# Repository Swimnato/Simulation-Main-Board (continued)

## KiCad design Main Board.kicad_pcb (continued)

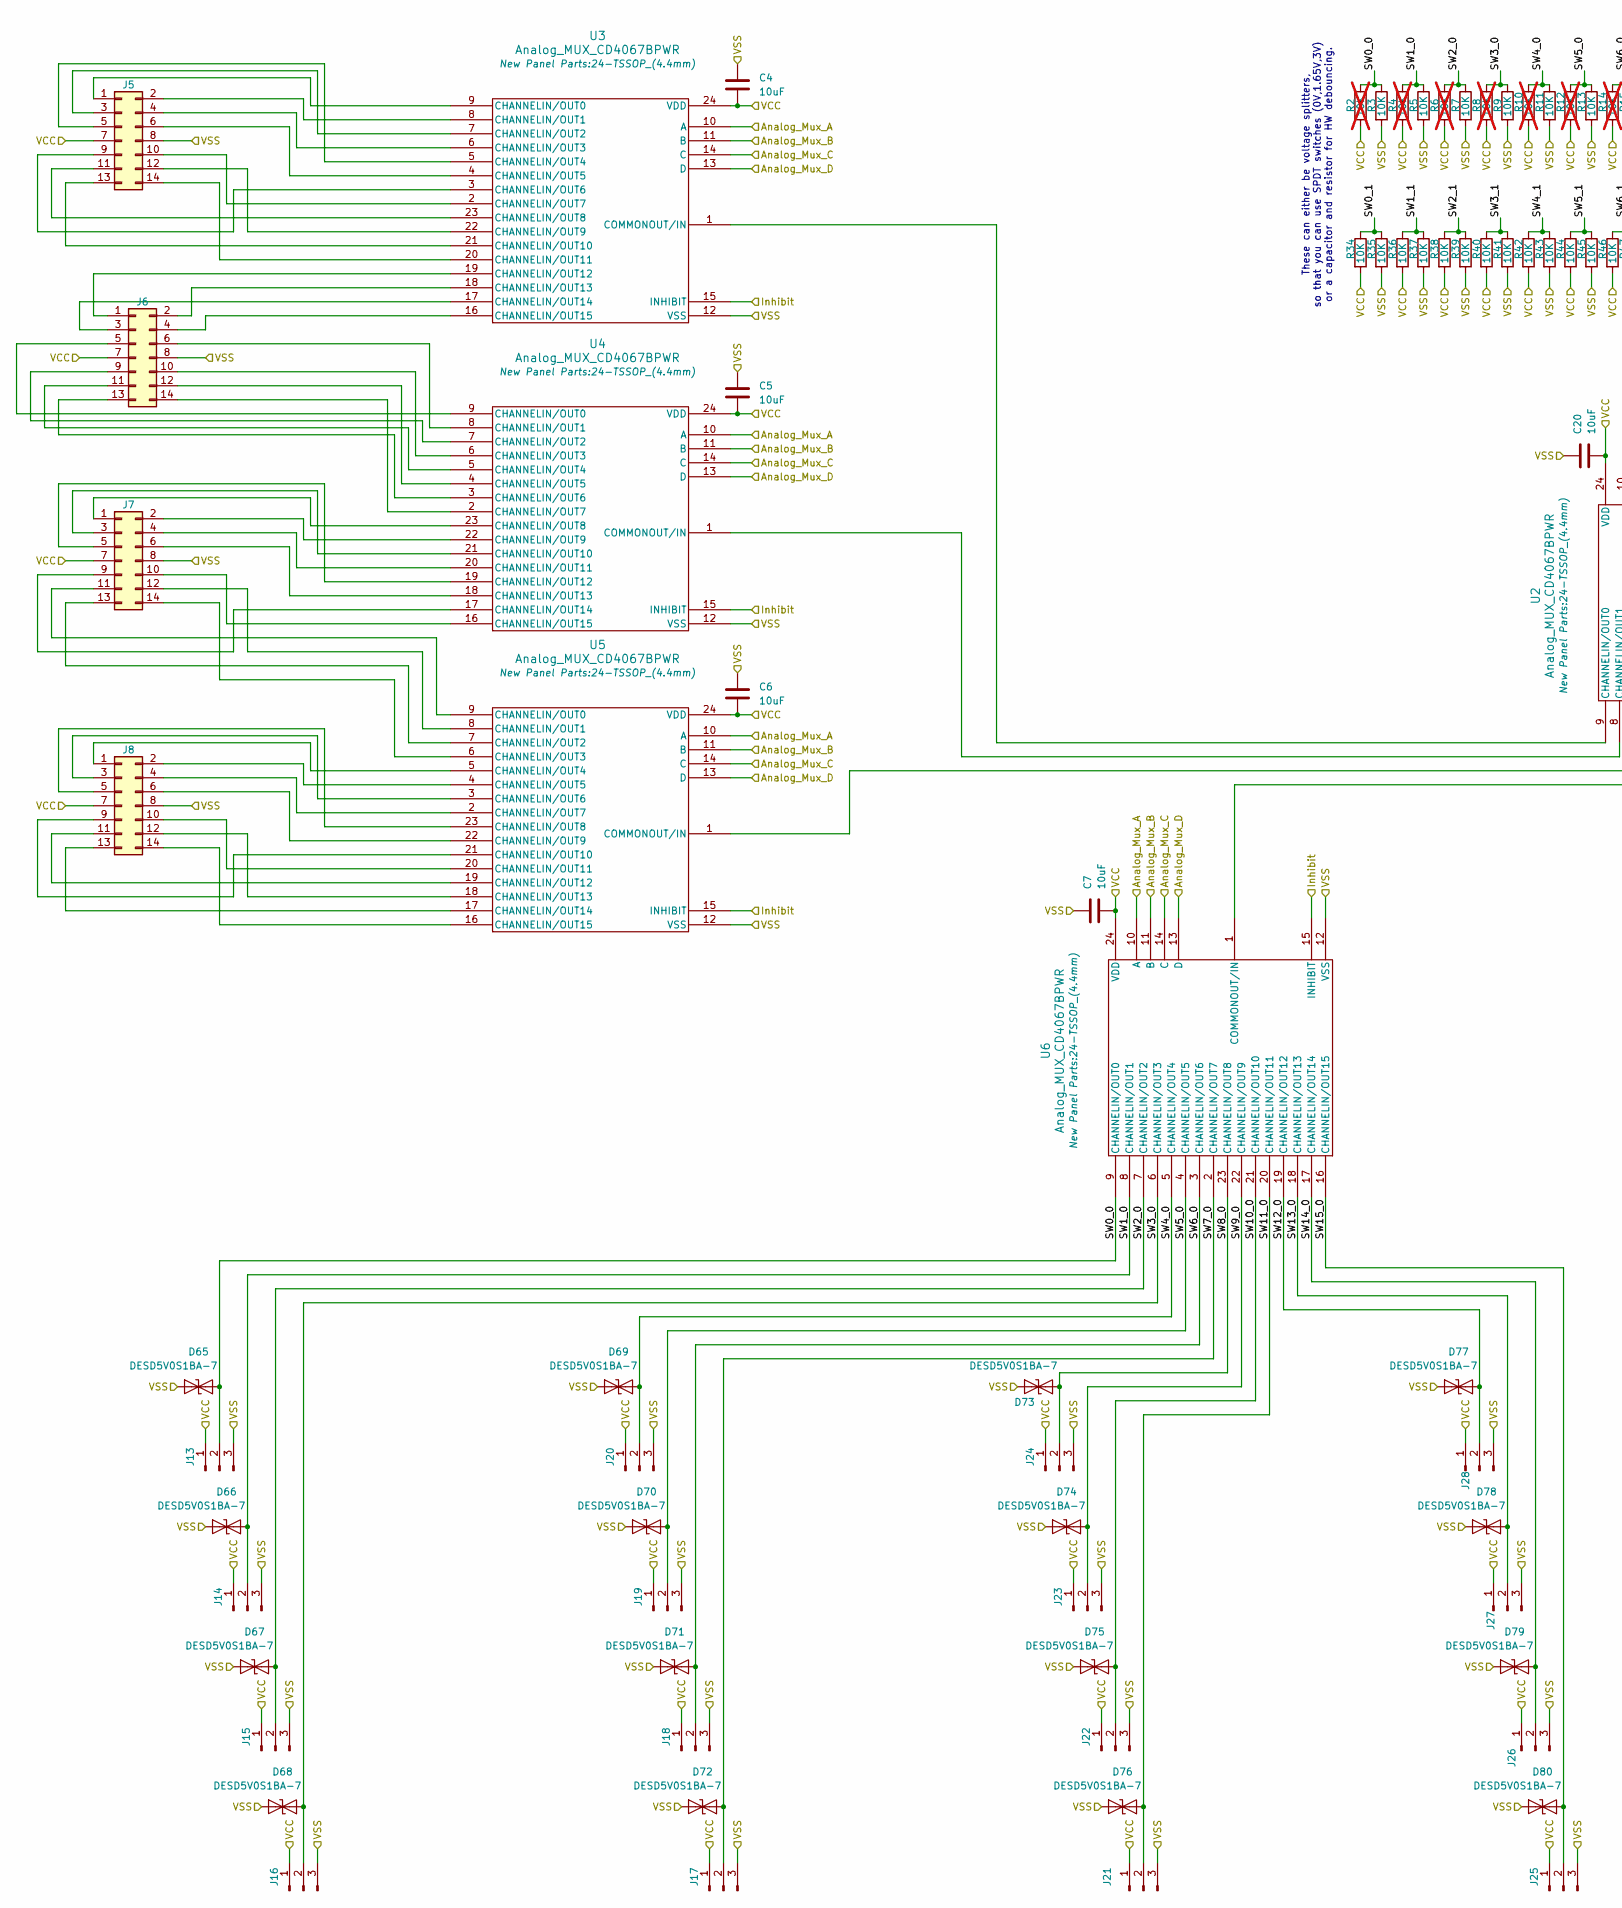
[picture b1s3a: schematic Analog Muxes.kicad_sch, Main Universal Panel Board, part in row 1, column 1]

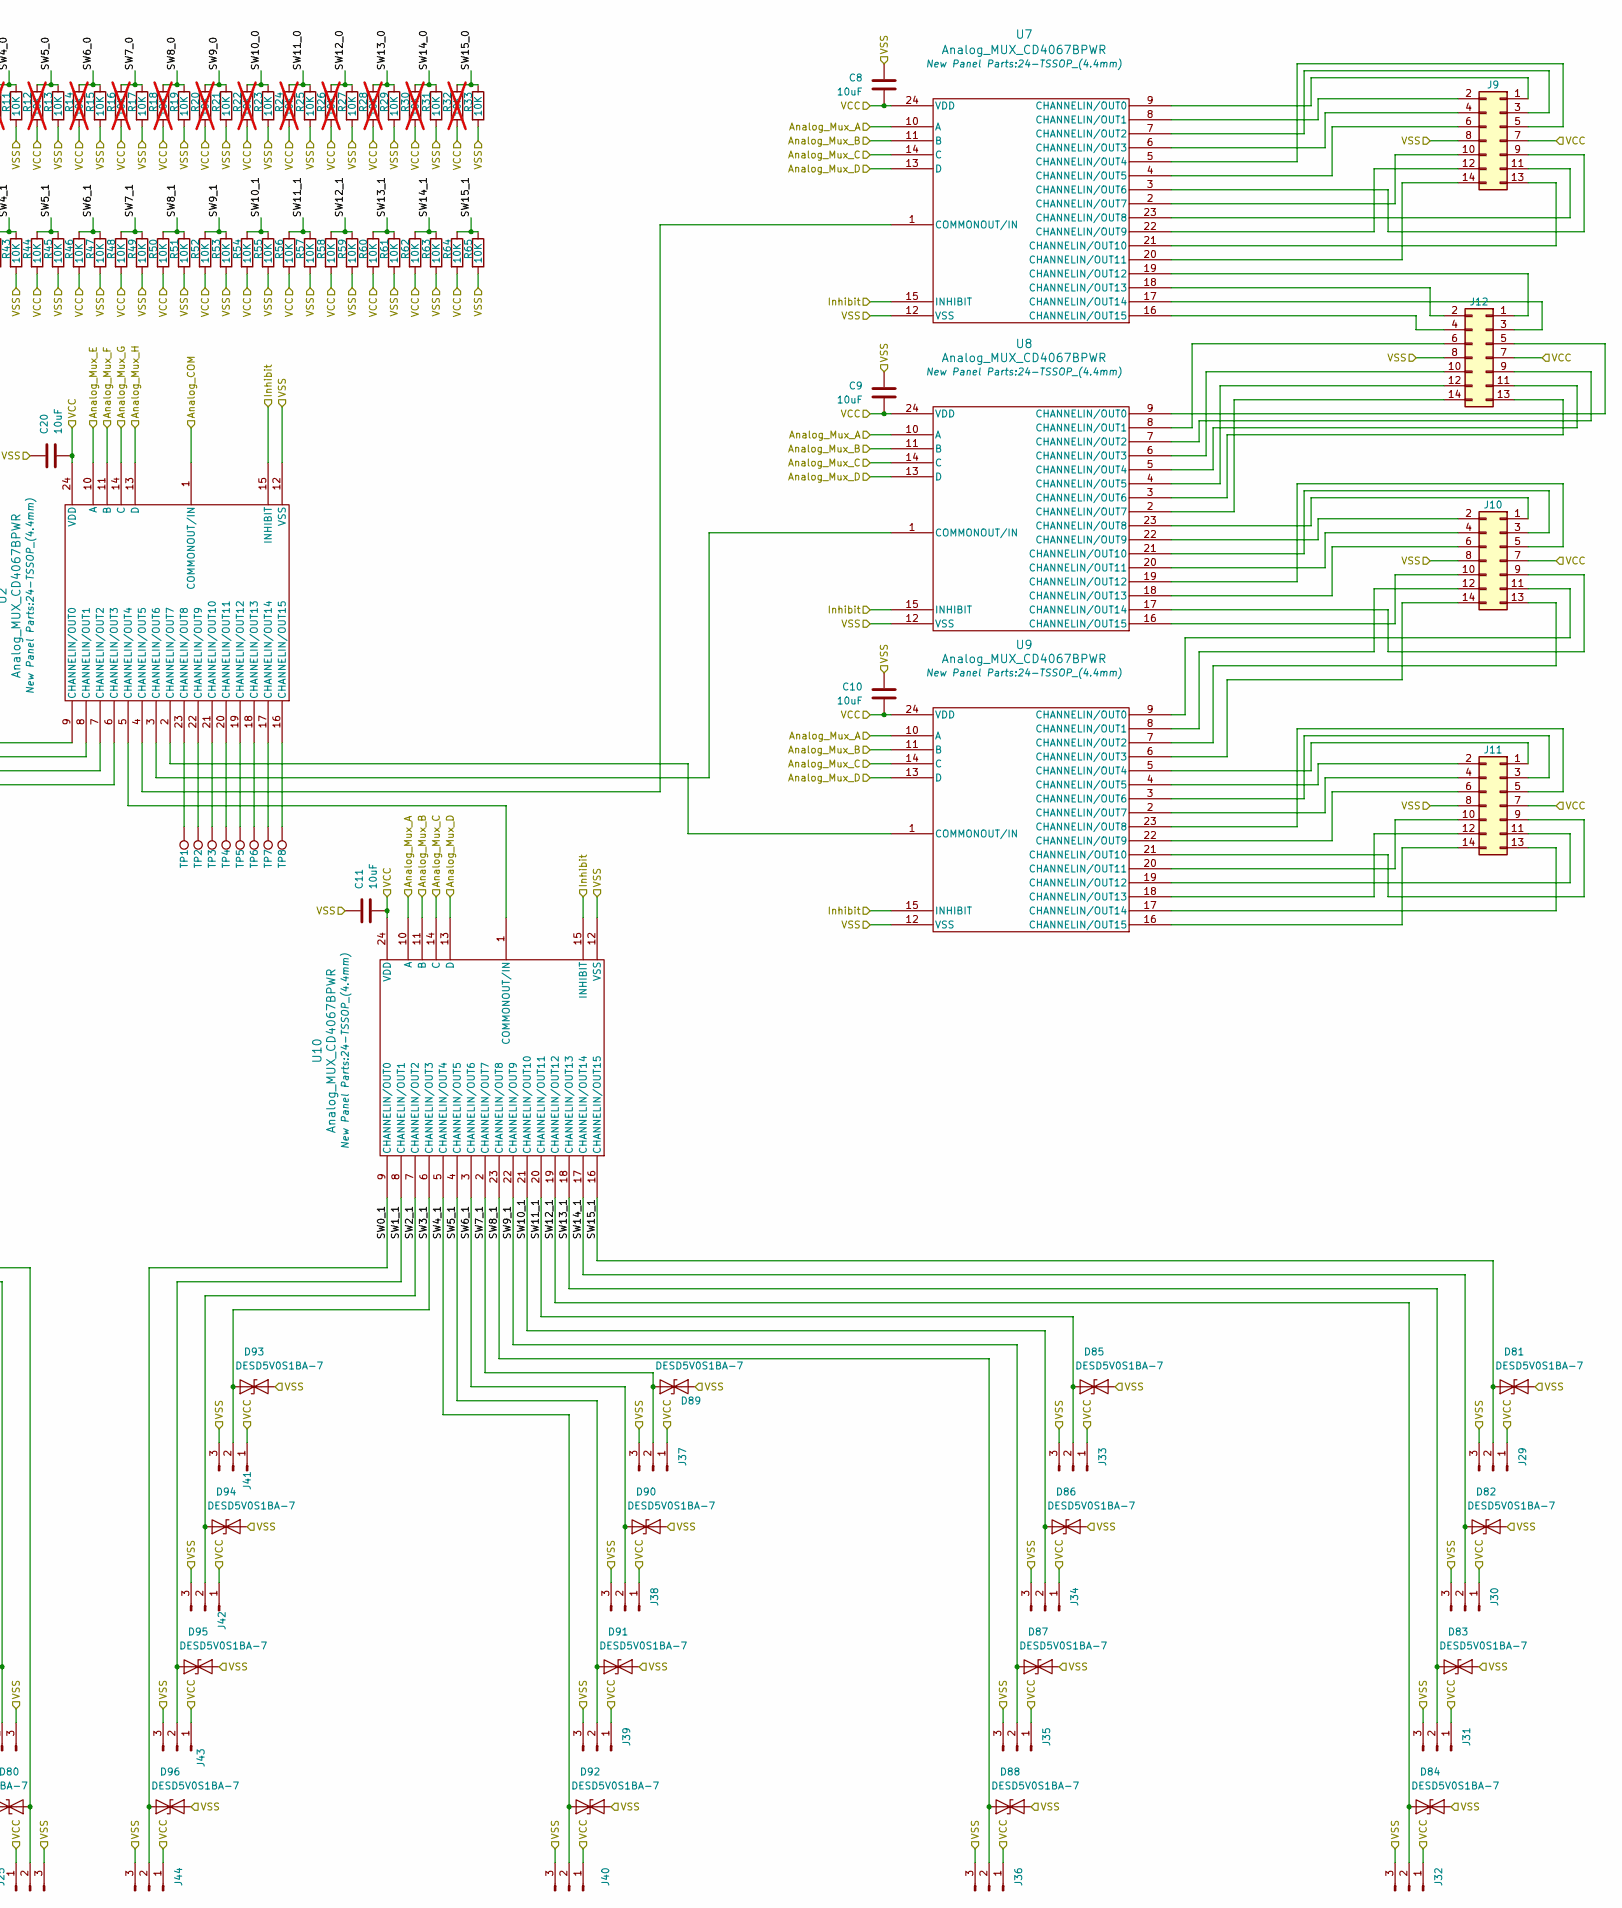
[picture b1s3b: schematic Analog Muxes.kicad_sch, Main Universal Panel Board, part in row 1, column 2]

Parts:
C4, C5, C6, C7, C8, C9, C10, C11, C20: 10uF; C_0805_2012Metric_Pad1.18x1.45mm_HandSolder
D65, D66, D67, D68, D69, D70, D71, D72, D73, D74, D75, D76, D77, D78, D79, D80, D81, D82, D83, D84, D85, D86, D87, D88, D89, D90, D91, D92, D93, D94, D95, D96: DESD5V0S1BA-7; D_SOD-323
J5, J6, J7, J8, J9, J10, J11, J12: Conn_02x07_Odd_Even; IDC-Header_2x07_P2.54mm_Vertical
J13, J14, J15, J16, J17, J18, J19, J20, J21, J22, J23, J24, J25, J26, J27, J28, J29, J30, J31, J32, J33, J34, J35, J36, J37, J38, J39, J40, J41, J42, J43, J44: Conn_01x03_Pin; JST_PH_B3B-PH-K_1x03_P2.00mm_Vertical
R2, R4, R6, R8, R10, R12, R14, R16, R18, R20, R22, R24, R26, R28, R30, R32: 10K; R_0603_1608Metric; not fitted
R3, R5, R7, R9, R11, R13, R15, R17, R19, R21, R23, R25, R27, R29, R31, R33, R34, R35, R36, R37, R38, R39, R40, R41, R42, R43, R44, R45, R46, R47, R48, R49, R50, R51, R52, R53, R54, R55, R56, R57, R58, R59, R60, R61, R62, R63, R64, R65: 10K; R_0603_1608Metric
TP1, TP2, TP3, TP4, TP5, TP6, TP7, TP8: TestPoint; Pin_D1.0mm_L10.0mm
U2, U3, U4, U5, U6, U7, U8, U9, U10: Analog_MUX_CD4067BPWR; 24-TSSOP_(4.4mm); Manufacturer Part Number CD4067BPWR

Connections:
+3.3V: C4.2, C5.2, C6.2, C7.2, C8.2, C9.2, C10.2, C11.2, C20.2, J5.7, J6.7, J7.7, J8.7, J9.7, J10.7, J11.7, J12.7, J13.1, J14.1, J15.1, J16.1, J17.1, J18.1, J19.1, J20.1, J21.1, J22.1, J23.1, J24.1, J25.1, J26.1, J27.1, J28.1, J29.1, J30.1, J31.1, J32.1, J33.1, J34.1, J35.1, J36.1, J37.1, J38.1, J39.1, J40.1, J41.1, J42.1, J43.1, J44.1, R2.2, R4.2, R6.2, R8.2, R10.2, R12.2, R14.2, R16.2, R18.2, R20.2, R22.2, R24.2, R26.2, R28.2, R30.2, R32.2, R34.2, R36.2, R38.2, R40.2, R42.2, R44.2, R46.2, R48.2, R50.2, R52.2, R54.2, R56.2, R58.2, R60.2, R62.2, R64.2, U2.24 (VDD), U3.24 (VDD), U4.24 (VDD), U5.24 (VDD), U6.24 (VDD), U7.24 (VDD), U8.24 (VDD), U9.24 (VDD), U10.24 (VDD); also elsewhere on the board
/Analog Input Mux/Analog_COM: U2.1 (COMMONOUT/IN); also elsewhere on the board
/Analog Input Mux/Analog_Mux_A: U3.10 (A), U4.10 (A), U5.10 (A), U6.10 (A), U7.10 (A), U8.10 (A), U9.10 (A), U10.10 (A); also elsewhere on the board
/Analog Input Mux/Analog_Mux_B: U3.11 (B), U4.11 (B), U5.11 (B), U6.11 (B), U7.11 (B), U8.11 (B), U9.11 (B), U10.11 (B); also elsewhere on the board
/Analog Input Mux/Analog_Mux_C: U3.14 (C), U4.14 (C), U5.14 (C), U6.14 (C), U7.14 (C), U8.14 (C), U9.14 (C), U10.14 (C); also elsewhere on the board
/Analog Input Mux/Analog_Mux_D: U3.13 (D), U4.13 (D), U5.13 (D), U6.13 (D), U7.13 (D), U8.13 (D), U9.13 (D), U10.13 (D); also elsewhere on the board
/Analog Input Mux/Analog_Mux_E: U2.10 (A); also elsewhere on the board
/Analog Input Mux/Analog_Mux_F: U2.11 (B); also elsewhere on the board
/Analog Input Mux/Analog_Mux_G: U2.14 (C); also elsewhere on the board
/Analog Input Mux/Analog_Mux_H: U2.13 (D); also elsewhere on the board
/Analog Input Mux/Inhibit: U2.15 (INHIBIT), U3.15 (INHIBIT), U4.15 (INHIBIT), U5.15 (INHIBIT), U6.15 (INHIBIT), U7.15 (INHIBIT), U8.15 (INHIBIT), U9.15 (INHIBIT), U10.15 (INHIBIT); also elsewhere on the board
/Analog Input Mux/SW0_0: D65.1 (A1), J13.2, R2.1, R3.1, U6.9 (CHANNELIN/OUT0)
/Analog Input Mux/SW0_1: D96.1 (A1), J44.2, R34.1, R35.1, U10.9 (CHANNELIN/OUT0)
/Analog Input Mux/SW1_0: D66.1 (A1), J14.2, R4.1, R5.1, U6.8 (CHANNELIN/OUT1)
/Analog Input Mux/SW1_1: D95.1 (A1), J43.2, R36.1, R37.1, U10.8 (CHANNELIN/OUT1)
/Analog Input Mux/SW2_0: D67.1 (A1), J15.2, R6.1, R7.1, U6.7 (CHANNELIN/OUT2)
/Analog Input Mux/SW2_1: D94.1 (A1), J42.2, R38.1, R39.1, U10.7 (CHANNELIN/OUT2)
/Analog Input Mux/SW3_0: D68.1 (A1), J16.2, R8.1, R9.1, U6.6 (CHANNELIN/OUT3)
/Analog Input Mux/SW3_1: D93.1 (A1), J41.2, R40.1, R41.1, U10.6 (CHANNELIN/OUT3)
/Analog Input Mux/SW4_0: D69.1 (A1), J20.2, R10.1, R11.1, U6.5 (CHANNELIN/OUT4)
/Analog Input Mux/SW4_1: D92.1 (A1), J40.2, R42.1, R43.1, U10.5 (CHANNELIN/OUT4)
/Analog Input Mux/SW5_0: D70.1 (A1), J19.2, R12.1, R13.1, U6.4 (CHANNELIN/OUT5)
/Analog Input Mux/SW5_1: D91.1 (A1), J39.2, R44.1, R45.1, U10.4 (CHANNELIN/OUT5)
/Analog Input Mux/SW6_0: D71.1 (A1), J18.2, R14.1, R15.1, U6.3 (CHANNELIN/OUT6)
/Analog Input Mux/SW6_1: D90.1 (A1), J38.2, R46.1, R47.1, U10.3 (CHANNELIN/OUT6)
/Analog Input Mux/SW7_0: D72.1 (A1), J17.2, R16.1, R17.1, U6.2 (CHANNELIN/OUT7)
/Analog Input Mux/SW7_1: D89.1 (A1), J37.2, R48.1, R49.1, U10.2 (CHANNELIN/OUT7)
/Analog Input Mux/SW8_0: D73.1 (A1), J24.2, R18.1, R19.1, U6.23 (CHANNELIN/OUT8)
/Analog Input Mux/SW8_1: D88.1 (A1), J36.2, R50.1, R51.1, U10.23 (CHANNELIN/OUT8)
/Analog Input Mux/SW9_0: D74.1 (A1), J23.2, R20.1, R21.1, U6.22 (CHANNELIN/OUT9)
/Analog Input Mux/SW9_1: D87.1 (A1), J35.2, R52.1, R53.1, U10.22 (CHANNELIN/OUT9)
/Analog Input Mux/SW10_0: D75.1 (A1), J22.2, R22.1, R23.1, U6.21 (CHANNELIN/OUT10)
/Analog Input Mux/SW10_1: D86.1 (A1), J34.2, R54.1, R55.1, U10.21 (CHANNELIN/OUT10)
/Analog Input Mux/SW11_0: D76.1 (A1), J21.2, R24.1, R25.1, U6.20 (CHANNELIN/OUT11)
/Analog Input Mux/SW11_1: D85.1 (A1), J33.2, R56.1, R57.1, U10.20 (CHANNELIN/OUT11)
/Analog Input Mux/SW12_0: D77.1 (A1), J28.2, R26.1, R27.1, U6.19 (CHANNELIN/OUT12)
/Analog Input Mux/SW12_1: D84.1 (A1), J32.2, R58.1, R59.1, U10.19 (CHANNELIN/OUT12)
/Analog Input Mux/SW13_0: D78.1 (A1), J27.2, R28.1, R29.1, U6.18 (CHANNELIN/OUT13)
/Analog Input Mux/SW13_1: D83.1 (A1), J31.2, R60.1, R61.1, U10.18 (CHANNELIN/OUT13)
/Analog Input Mux/SW14_0: D79.1 (A1), J26.2, R30.1, R31.1, U6.17 (CHANNELIN/OUT14)
/Analog Input Mux/SW14_1: D82.1 (A1), J30.2, R62.1, R63.1, U10.17 (CHANNELIN/OUT14)
/Analog Input Mux/SW15_0: D80.1 (A1), J25.2, R32.1, R33.1, U6.16 (CHANNELIN/OUT15)
/Analog Input Mux/SW15_1: D81.1 (A1), J29.2, R64.1, R65.1, U10.16 (CHANNELIN/OUT15)
GND: C4.1, C5.1, C6.1, C7.1, C8.1, C9.1, C10.1, C11.1, C20.1, D65.2 (A2), D66.2 (A2), D67.2 (A2), D68.2 (A2), D69.2 (A2), D70.2 (A2), D71.2 (A2), D72.2 (A2), D73.2 (A2), D74.2 (A2), D75.2 (A2), D76.2 (A2), D77.2 (A2), D78.2 (A2), D79.2 (A2), D80.2 (A2), D81.2 (A2), D82.2 (A2), D83.2 (A2), D84.2 (A2), D85.2 (A2), D86.2 (A2), D87.2 (A2), D88.2 (A2), D89.2 (A2), D90.2 (A2), D91.2 (A2), D92.2 (A2), D93.2 (A2), D94.2 (A2), D95.2 (A2), D96.2 (A2), J5.8, J6.8, J7.8, J8.8, J9.8, J10.8, J11.8, J12.8, J13.3, J14.3, J15.3, J16.3, J17.3, J18.3, J19.3, J20.3, J21.3, J22.3, J23.3, J24.3, J25.3, J26.3, J27.3, J28.3, J29.3, J30.3, J31.3, J32.3, J33.3, J34.3, J35.3, J36.3, J37.3, J38.3, J39.3, J40.3, J41.3, J42.3, J43.3, J44.3, R3.2, R5.2, R7.2, R9.2, R11.2, R13.2, R15.2, R17.2, R19.2, R21.2, R23.2, R25.2, R27.2, R29.2, R31.2, R33.2, R35.2, R37.2, R39.2, R41.2, R43.2, R45.2, R47.2, R49.2, R51.2, R53.2, R55.2, R57.2, R59.2, R61.2, R63.2, R65.2, U2.12 (VSS), U3.12 (VSS), U4.12 (VSS), U5.12 (VSS), U6.12 (VSS), U7.12 (VSS), U8.12 (VSS), U9.12 (VSS), U10.12 (VSS); also elsewhere on the board
unnamed: J5.1, U3.9 (CHANNELIN/OUT0)
unnamed: J5.2, U3.8 (CHANNELIN/OUT1)
unnamed: J5.3, U3.7 (CHANNELIN/OUT2)
unnamed: J5.4, U3.6 (CHANNELIN/OUT3)
unnamed: J5.5, U3.5 (CHANNELIN/OUT4)
unnamed: J5.6, U3.4 (CHANNELIN/OUT5)
unnamed: J5.9, U3.3 (CHANNELIN/OUT6)
unnamed: J5.10, U3.2 (CHANNELIN/OUT7)
unnamed: J5.11, U3.23 (CHANNELIN/OUT8)
unnamed: J5.12, U3.22 (CHANNELIN/OUT9)
unnamed: J5.13, U3.21 (CHANNELIN/OUT10)
unnamed: J5.14, U3.20 (CHANNELIN/OUT11)
unnamed: J6.1, U3.19 (CHANNELIN/OUT12)
unnamed: J6.2, U3.18 (CHANNELIN/OUT13)
unnamed: J6.3, U3.17 (CHANNELIN/OUT14)
unnamed: J6.4, U3.16 (CHANNELIN/OUT15)
unnamed: J6.5, U4.9 (CHANNELIN/OUT0)
unnamed: J6.6, U4.8 (CHANNELIN/OUT1)
unnamed: J6.9, U4.7 (CHANNELIN/OUT2)
unnamed: J6.10, U4.6 (CHANNELIN/OUT3)
unnamed: J6.11, U4.5 (CHANNELIN/OUT4)
unnamed: J6.12, U4.4 (CHANNELIN/OUT5)
unnamed: J6.13, U4.3 (CHANNELIN/OUT6)
unnamed: J6.14, U4.2 (CHANNELIN/OUT7)
unnamed: J7.1, U4.23 (CHANNELIN/OUT8)
unnamed: J7.2, U4.22 (CHANNELIN/OUT9)
unnamed: J7.3, U4.21 (CHANNELIN/OUT10)
unnamed: J7.4, U4.20 (CHANNELIN/OUT11)
unnamed: J7.5, U4.19 (CHANNELIN/OUT12)
unnamed: J7.6, U4.18 (CHANNELIN/OUT13)
unnamed: J7.9, U4.17 (CHANNELIN/OUT14)
unnamed: J7.10, U4.16 (CHANNELIN/OUT15)
unnamed: J7.11, U5.9 (CHANNELIN/OUT0)
unnamed: J7.12, U5.8 (CHANNELIN/OUT1)
unnamed: J7.13, U5.7 (CHANNELIN/OUT2)
unnamed: J7.14, U5.6 (CHANNELIN/OUT3)
unnamed: J8.1, U5.5 (CHANNELIN/OUT4)
unnamed: J8.2, U5.4 (CHANNELIN/OUT5)
unnamed: J8.3, U5.3 (CHANNELIN/OUT6)
unnamed: J8.4, U5.2 (CHANNELIN/OUT7)
unnamed: J8.5, U5.23 (CHANNELIN/OUT8)
unnamed: J8.6, U5.22 (CHANNELIN/OUT9)
unnamed: J8.9, U5.21 (CHANNELIN/OUT10)
unnamed: J8.10, U5.20 (CHANNELIN/OUT11)
unnamed: J8.11, U5.19 (CHANNELIN/OUT12)
unnamed: J8.12, U5.18 (CHANNELIN/OUT13)
unnamed: J8.13, U5.17 (CHANNELIN/OUT14)
unnamed: J8.14, U5.16 (CHANNELIN/OUT15)
unnamed: J9.1, U7.9 (CHANNELIN/OUT0)
unnamed: J9.2, U7.8 (CHANNELIN/OUT1)
unnamed: J9.3, U7.7 (CHANNELIN/OUT2)
unnamed: J9.4, U7.6 (CHANNELIN/OUT3)
unnamed: J9.5, U7.5 (CHANNELIN/OUT4)
unnamed: J9.6, U7.4 (CHANNELIN/OUT5)
unnamed: J9.9, U7.3 (CHANNELIN/OUT6)
unnamed: J9.10, U7.2 (CHANNELIN/OUT7)
unnamed: J9.11, U7.23 (CHANNELIN/OUT8)
unnamed: J9.12, U7.22 (CHANNELIN/OUT9)
unnamed: J9.13, U7.21 (CHANNELIN/OUT10)
unnamed: J9.14, U7.20 (CHANNELIN/OUT11)
unnamed: J10.1, U8.23 (CHANNELIN/OUT8)
unnamed: J10.2, U8.22 (CHANNELIN/OUT9)
unnamed: J10.3, U8.21 (CHANNELIN/OUT10)
unnamed: J10.4, U8.20 (CHANNELIN/OUT11)
unnamed: J10.5, U8.19 (CHANNELIN/OUT12)
unnamed: J10.6, U8.18 (CHANNELIN/OUT13)
unnamed: J10.9, U8.17 (CHANNELIN/OUT14)
unnamed: J10.10, U8.16 (CHANNELIN/OUT15)
unnamed: J10.11, U9.9 (CHANNELIN/OUT0)
unnamed: J10.12, U9.8 (CHANNELIN/OUT1)
unnamed: J10.13, U9.7 (CHANNELIN/OUT2)
unnamed: J10.14, U9.6 (CHANNELIN/OUT3)
unnamed: J11.1, U9.5 (CHANNELIN/OUT4)
unnamed: J11.2, U9.4 (CHANNELIN/OUT5)
unnamed: J11.3, U9.3 (CHANNELIN/OUT6)
unnamed: J11.4, U9.2 (CHANNELIN/OUT7)
unnamed: J11.5, U9.23 (CHANNELIN/OUT8)
unnamed: J11.6, U9.22 (CHANNELIN/OUT9)
unnamed: J11.9, U9.21 (CHANNELIN/OUT10)
unnamed: J11.10, U9.20 (CHANNELIN/OUT11)
unnamed: J11.11, U9.19 (CHANNELIN/OUT12)
unnamed: J11.12, U9.18 (CHANNELIN/OUT13)
unnamed: J11.13, U9.17 (CHANNELIN/OUT14)
unnamed: J11.14, U9.16 (CHANNELIN/OUT15)
unnamed: J12.1, U7.19 (CHANNELIN/OUT12)
unnamed: J12.2, U7.18 (CHANNELIN/OUT13)
unnamed: J12.3, U7.17 (CHANNELIN/OUT14)
unnamed: J12.4, U7.16 (CHANNELIN/OUT15)
unnamed: J12.5, U8.9 (CHANNELIN/OUT0)
unnamed: J12.6, U8.8 (CHANNELIN/OUT1)
unnamed: J12.9, U8.7 (CHANNELIN/OUT2)
unnamed: J12.10, U8.6 (CHANNELIN/OUT3)
unnamed: J12.11, U8.5 (CHANNELIN/OUT4)
unnamed: J12.12, U8.4 (CHANNELIN/OUT5)
unnamed: J12.13, U8.3 (CHANNELIN/OUT6)
unnamed: J12.14, U8.2 (CHANNELIN/OUT7)
unnamed: U2.9 (CHANNELIN/OUT0), U3.1 (COMMONOUT/IN)
unnamed: U2.8 (CHANNELIN/OUT1), U4.1 (COMMONOUT/IN)
unnamed: U2.7 (CHANNELIN/OUT2), U5.1 (COMMONOUT/IN)
unnamed: U2.6 (CHANNELIN/OUT3), U6.1 (COMMONOUT/IN)
unnamed: U2.4 (CHANNELIN/OUT5), U7.1 (COMMONOUT/IN)
unnamed: U2.3 (CHANNELIN/OUT6), U8.1 (COMMONOUT/IN)
unnamed: U2.2 (CHANNELIN/OUT7), U9.1 (COMMONOUT/IN)
unnamed: TP1.1, U2.23 (CHANNELIN/OUT8)
unnamed: TP2.1, U2.22 (CHANNELIN/OUT9)
unnamed: TP3.1, U2.21 (CHANNELIN/OUT10)
unnamed: TP4.1, U2.20 (CHANNELIN/OUT11)
unnamed: TP5.1, U2.19 (CHANNELIN/OUT12)
unnamed: TP6.1, U2.18 (CHANNELIN/OUT13)
unnamed: TP7.1, U2.17 (CHANNELIN/OUT14)
unnamed: TP8.1, U2.16 (CHANNELIN/OUT15)
unnamed: U2.5 (CHANNELIN/OUT4), U10.1 (COMMONOUT/IN)

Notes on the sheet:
These can either be voltage splitters, so that you can use SPDT switches (0V,1.65V,3V) or a capacitor and resistor for HW debouncing.

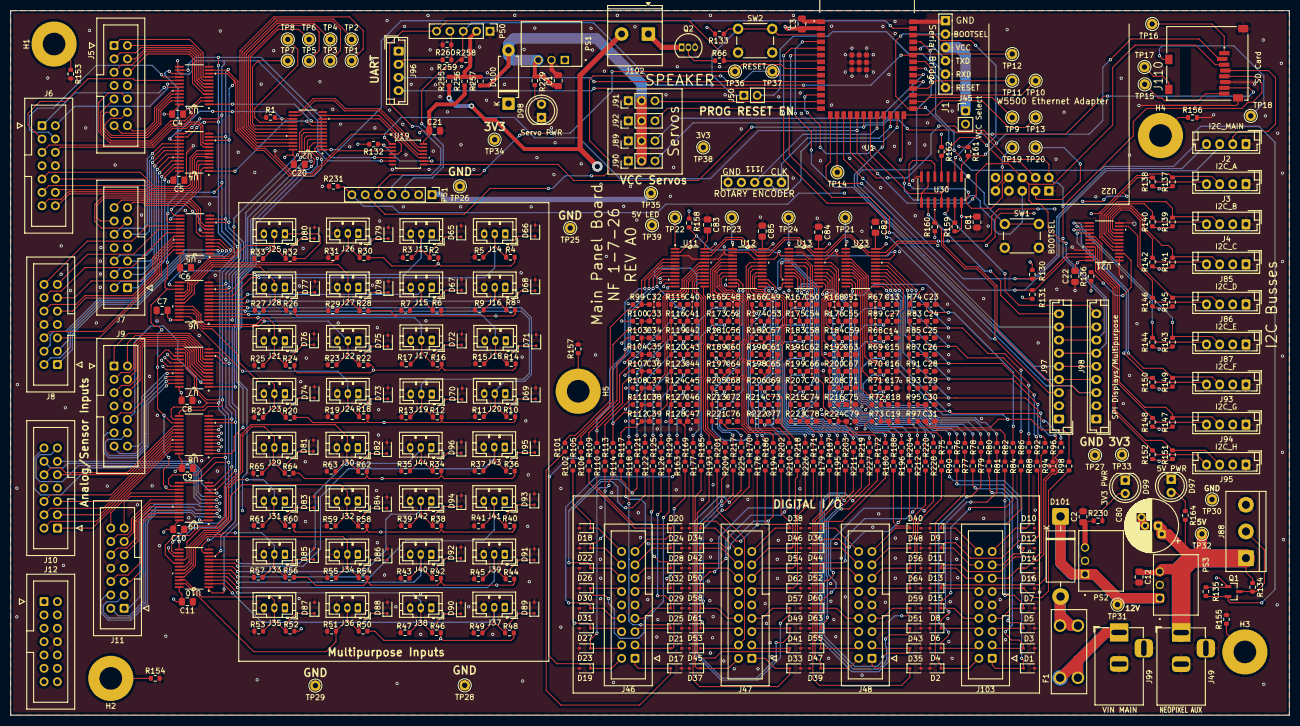
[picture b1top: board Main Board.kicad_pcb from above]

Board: 4 copper layers, 243.2 x 134.0 mm, 564 parts (0 on the bottom side), 363 nets.

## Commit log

2025-09-20 Move Over from subsytem repo
    This was moved over from the subsystem repository in the osirus project. It is better suited here alone in its own repo
2025-09-20 Refining BOM & X4
    X4 included a diode to protect from reverse polarity DC input. Begun work on Digikey BOM
2025-09-20 Refined BOM
    Adjusted BOM to have all parts
2025-10-10 Started HW Testing
    Started HW testing and on main sim board library.
2025-10-10 Added GitIgnore
2025-10-10 Fixed some typos in the pin definition
2025-10-11 started work on testing code
2025-10-12 wrote and organized more tests
2025-10-14 Finished Digital IO driver
2025-10-14 Wrote I2C Mux Code
2025-10-14 Added Second UART Code
2025-10-14 Began work on readmes
2025-10-17 Finished Test Code
    added to the readme as well, changed dependency to the adafruit fork of sdfat
2025-10-19 updated test code
2026-01-07 Rev A0
    REV A0 changes, additionally added STEP files for PAM8302, MAX98357, and JST XH 4 connector for UART. Updated KiCad schematic and PCB files, reorganized BOM and pick-and-place files for new revisions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
2026-01-08 Finished Release Package
2026-01-08 Made Instructions more clear
2026-01-09 Added 2 test points
    for possible logic level converters
